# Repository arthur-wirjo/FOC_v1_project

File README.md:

# DIY FOC Motor Controller V1: Custom Hardware & Firmware from Scratch 

A custom-designed, 60V 50A Field Oriented Control (FOC) BLDC motor controller built from scratch. Designed for high-performance robotics, featuring a 4-layer power PCB, isolated USB telemetry, and CAN bus communication.

## Overview

I started this project to deeply understand the hardware architecture of modern, high-power motor drivers like the VESC and ODrive. Instead of just buying an off-the-shelf driver, I wanted to design one from the ground up to learn the intricacies of power electronics, mixed-signal PCB layout, gate driving, and hardware debugging.

The system is split into a 4-layer main power board (handling the MCU and 60V power stage) and a separate 2-layer magnetic encoder board mounted directly to the motor. This approach kept the overall footprint compact and reduced manufacturing costs.

As the project progressed, it evolved beyond "build a VESC clone" into writing a full custom bare-metal FOC firmware stack from scratch. As of October 3, 2026, the board successfully runs closed-loop Field-Oriented Control, achieving smooth velocity control. Having fulfilled its purpose as a deep-dive educational tool into power electronics and motor control theory, **this project is now officially concluded**. The repository remains as a documented post-mortem and reference for DIY FOC development.

## Key Features

* **Working Closed-Loop FOC:** Fully custom bare-metal firmware achieves smooth closed-loop current control and velocity control.
* **60V Power Stage:** 60V-rated MOSFETs capable of handling 10S Li-Po battery voltages and regenerative braking spikes.
* **Precision Current Sensing:** 1mΩ shunt resistors utilizing strict Kelvin connections and RC-filtered differential amplifiers.
* **Isolated Telemetry:** ADuM3160-based USB isolation to protect the host computer from catastrophic 60V transients during live tuning.
* **Robust Communication:** TJA1051T/3 CAN bus transceiver with 120Ω termination for robot networking.
* **Modular Encoder:** Separate 2-layer AS5048A magnetic encoder PCB using JST-GH SMD connectors.

## Hardware

### Computing & Control
* **Microcontroller:** STM32F405RGT6 (Chosen for its floating-point unit, advanced motor control timers, and native VESC compatibility)
* **Gate Driver:** TI DRV8301 (Features a built-in 5V buck converter and dual current shunt amplifiers. Chosen over the DRV8323 for VESC compatibility)

### Power Stage
* **MOSFETs:** Infineon IRFS7530 in D2PAK-7 (Rated for 60V, providing ample headroom for a 10S ~40V battery and regenerative braking)
* **Current Sense:** Yageo PU2512FK-070R001L (1mΩ, 2W metal alloy shunts)
* **Protection:** Littelfuse SMCJ43A TVS Diode (Clamps dangerous voltage spikes generated by motor back-EMF during hard braking)
* **Connectors:** Amass XT90-S (Anti-spark) for battery input

### Sensing & Telemetry
* **Encoder:** AMS AS5048A (14-bit absolute magnetic encoder reading a 6x2.5mm diametrically magnetized NdFeB magnet)
* **Temperature:** Murata 10kΩ 0603 NTC Thermistor (Placed directly adjacent to the MOSFETs to monitor power stage thermals)
* **Voltage Sensing:** 39kΩ / 2.2kΩ voltage divider to safely scale the 60V bus down to the STM32's 3.3V ADC range

## PCB Design & Layout

The board utilizes a 4-layer stackup to safely separate high-current paths from delicate digital signals:
* **Layer 1 (Top):** Components, massive copper polygons for Motor Phases and 42V supply.
* **Layer 2 (Inner 1):** Solid GND plane (Acts as an EMI shield for the signal layer).
* **Layer 3 (Inner 2):** Signal routing (SPI, CAN, Gate Drive traces).
* **Layer 4 (Bottom):** Additional GND and 42V copper pours, heavily via-stitched to the top layer to maximize current carrying capacity and thermal dissipation.

## Challenges and Lessons Learned

Building a high-power motor controller from scratch provided an intense, hands-on education in hardware and firmware debugging.

### Solder Wicking and Clearance Tolerances (V1.0)
After freshly soldering the V1.0 PCB, I felt an unusually strong resistance when I tried to rotate the motor by hand. I learned this is caused by back-EMF when phase wires are shorted together. Multimeter testing confirmed that V++, GND, and all three motor phases were dead-shorted.

Upon inspection, I realized the clearance between my GND copper pour and the soldering pads for V++ and the phase wires was very small (0.15mm). When hand-soldering the massive motor wires, the liquid solder easily wicked across that tiny gap into the GND pour.

For V1.1, I redesigned the board with strict Net Classes, increasing the clearance around high-power wire pads to 0.6mm to create a physical "moat", while keeping the MCU digital clearance at 0.15mm for dense routing.

### The "Bad Internet Symbol" Trap (V1.1)
After successfully assembling V1.1 with new stencils and corrected clearances, the board still exhibited a short between V++, GND, and the phase wires.

I started isolating the issue by desoldering components one by one. I checked a bare V1.0 board and found no shorts, meaning the layout itself wasn't fundamentally shorted. I desoldered the MCU and gate driver — the short was still there. Finally, I desoldered the high-side MOSFETs one by one. Removing the last high-side MOSFET finally severed the short between V++ and the motor phases.

I probed the desoldered MOSFET and found a short between Pin 7 and the Source pins (Pins 2-6). Initially, I thought the MOSFET had overheated and failed closed during hot-plate reflow. However, I looked into the Infineon datasheet and saw a catastrophic error in the third-party CAD symbol I had downloaded.

The symbol incorrectly labeled Pin 7 as "Drain". In reality, the D2PAK-7 package uses the large back EPAD as the Drain, and Pins 2 through 7 are *all* Source pins. Because I followed the flawed schematic, my PCB layout drew a massive copper pour that physically connected the Drain (EPAD) to the Source (Pin 7). The PCB itself was shorting the circuit by design, while the MOSFETs were actually unharmed.

**Lesson learned:** Never trust third-party CAD footprints without verifying against the manufacturer's datasheet.

### The USB D+/D- Swap (V1.2)
With the phase-short issue resolved, V1.2 soldered up cleanly with no shorts between V++, GND, or the phase wires. After hours of VESC firmware macro configuration, I successfully flashed VESC firmware onto the board. However, the board never enumerated over USB — nothing populated on the host PC.

I re-checked the firmware configuration and it looked correct, so I moved to the hardware. It turned out to be a wiring mistake on my end, though the confusing pin naming in the schematic symbol didn't help: instead of connecting DP1↔DP2 and DN1↔DN2 (the isolator-side and MCU-side USB differential pairs), I had wired DP1↔DN1 and DP2↔DN2 — crossing the differential pairs instead of linking them straight through. I corrected this for V1.3.

### The Mysterious Non-Enumerating USB (V1.3)
V1.3 fixed the DP/DN wiring mistake. USB still did not enumerate.

At this point I was confident the hardware was correct, so I wrote a minimal bare-metal STM32 firmware (via STM32CubeMX, STM32CubeIDE, and STM32CubeProgrammer) with nothing but a USB CDC "hello world" to test enumeration independently of VESC firmware. It worked immediately — the host PC detected the board and the virtual COM port came up cleanly. This confirmed the hardware (including the USB isolation and the DP/DN fix) was fine, and the problem was somewhere inside VESC firmware itself.

After a weekend of digging, my working theory is that VESC firmware assumes VBUS sensing on a specific pin by default, which on my board doesn't correspond to an actual VBUS-sensing net — that pin (PA9 / TIM1_CH2) is repurposed as a motor PWM output on my hardware. If VESC firmware is waiting on a VBUS-sense signal that physically doesn't exist on my board, USB enumeration would never complete, since the firmware assumes the connection is dead.

Rather than dig further into VESC's fairly large and unfamiliar codebase to patch around this, I decided to use this as an opportunity to learn embedded systems more deeply from first principles by writing my own bare-metal FOC firmware from scratch.

### The Deceiving Cogging Torque (Open-Loop Commutation)
After first achieving open-loop commutation, I later struggled to reproduce it and assumed something had regressed in the firmware. After investigation, I realized the real cause: during my initial successful test, the motor had warmed up from repeated open-loop parameter tuning, which reduced its cogging torque (magnetic detent force) enough for the open-loop drive to overcome it smoothly. On a cold motor, the same open-loop parameters weren't enough to break through cogging torque cleanly. This was a good reminder that motor behavior is temperature-dependent, and that "it worked once" isn't the same as "it's tuned correctly."

### Missing Bulk Decoupling Capacitor (Current Sensing Noise)
While debugging noisy phase current readings, a senior pointed out that the DRV8301's built-in 5V buck converter was missing a bulk decoupling capacitor on my board. Without it, switching-induced ripple on the 5V rail was likely feeding through to the gate driver's built-in current sense amplifiers, degrading signal quality. I added the missing capacitor directly onto the existing V1.3 board (Frankenstein-style, dead-bug soldered), which noticeably cleaned up the current readings enough for stable closed-loop control. This will be properly integrated into the layout for the next PCB revision.

### Current Sensing Offsets and Phase Anomalies (The Final Hurdle)
While closed-loop velocity control was achieved, the final hurdle involved anomalies in the low-side current sensing. Through telemetry analysis under load, I observed three distinct issues:
1. **DC Offsets:** Despite software calibration, i_a exhibited a heavy positive offset (min -0.05A, max 0.35A), i_b (calculated) had a heavy negative offset, and i_c was relatively balanced. This points to inherent analog front-end biases or layout-induced ground offsets.
2. **Noise:** Low-side sensing is notoriously susceptible to switching noise. Even with ADC sampling synchronized to the timer's update event (the "quiet window"), the raw data remained spiky, pushing the limits of the software's low-pass filters.
3. **The 180-Degree Phase Shift Anomaly:** Telemetry revealed that i_a and i_c appeared to be roughly 180 degrees out of phase, rather than the expected 120 degrees. Initially, one might suspect a flipped differential pair on the PCB, but mathematically, inverting a 120-degree signal results in a 300-degree (-60 degree) phase shift, not 180 degrees. This anomaly is much more likely an artifact of severe layout-induced noise, ground bounce, or the inherent limitations of low-side current sensing on a noisy DIY board skewing the reconstructed waveforms.

**Lesson learned:** Mixed-signal PCB layout for high-current switching requires extreme care. For V2, I would transition to in-line current sensing with dedicated isolated amplifiers, ensure perfectly matched differential pair routing for the shunts, and implement a more robust analog filtering stage.

## Custom Firmware Development

Since abandoning VESC firmware, I built a custom bare-metal firmware stack using STM32CubeMX, STM32CubeIDE, and FreeRTOS (for telemetry and state management), with the actual FOC control loop implemented as a hardware-timer/ADC-interrupt-driven routine.

### MCU Pinout

**PWM (TIM1, Center-Aligned, Complementary Outputs)**
| Pin | Function |
|---|---|
| PA8 | TIM1_CH1 |
| PA9 | TIM1_CH2 |
| PA10 | TIM1_CH3 |
| PB13 | TIM1_CH1N |
| PB14 | TIM1_CH2N |
| PB15 | TIM1_CH3N |

**ADC (Current & Voltage Sensing)**
| Pin | Function |
|---|---|
| PA0 | ADC1_IN0 — Phase A Current |
| PA1 | ADC2_IN1 — Phase C Current |
| PA2 | ADC3_IN2 — VBUS Voltage Sensing |
| PA3 | ADC3_IN3 — MOSFET Temperature |

**DRV8301 Gate Driver (SPI1)**
| Pin | Function |
|---|---|
| PC1 | EN_GATE |
| PC2 | DC_CAL |
| PC0 | nFAULT (EXTI0) |
| PB3 | SPI1_SCK |
| PB4 | SPI1_MISO |
| PB5 | SPI1_MOSI |
| PD2 | CS |

**Encoder (SPI3)**
| Pin | Function |
|---|---|
| PC10 | SPI3_SCK |
| PC11 | SPI3_MISO |
| PC12 | SPI3_MOSI |
| PA15 | CS |

**CAN**
| Pin | Function |
|---|---|
| PB8 | CAN1_RX |
| PB9 | CAN1_TX |

**USB**
| Pin | Function |
|---|---|
| PA11 | D- |
| PA12 | D+ |

> **Critical note:** VBUS sensing on PA9 is intentionally *not* used — PA9 is a motor PWM pin on this board (see the V1.3 debugging story above). USB is forced to enumerate without relying on VBUS sensing.

### STM32CubeMX Configuration Notes
* Deadtime configured on the PWM timer to prevent shoot-through.
* Center-aligned PWM mode for reduced current ripple.
* ADC sampling is hardware-synchronized to PWM switching using TIM1's "Update Event" as the ADC "Trigger Event Selection," so current is always sampled at a consistent point in the switching cycle.
* Third phase current is reconstructed using Kirchhoff's Current Law rather than measured directly (only two shunts are sensed).
* ADC current sensing uses **injected conversion mode** so it can be hardware-triggered directly by the timer.
* ADC interrupt enabled in NVIC settings for the current-sensing ADC.
* Encoder SPI configured with DMA in full-duplex master mode.
* USB configured using the USB CDC class for direct serial communication with the host PC.

### Firmware Development Progress
1. ✅ Pinout and hardware configuration in CubeMX
2. ✅ USB CDC enumeration working
3. ✅ DRV8301 register read helper function + gate driver wake-up sequence
4. ✅ SPI encoder DMA callback
5. ✅ Open-loop SPWM commutation and tuning
6. ✅ DRV8301 register write helper function for current amplifier gain configuration
7. ✅ ADC hardware interrupt callback for current sensing (`HAL_ADC_ConvCpltCallback`)
8. ✅ FOC algorithm implemented inside `HAL_ADC_ConvCpltCallback`
9. ✅ Closed-loop current control achieved
10. ✅ Closed-loop velocity control achieved — smooth motor spin under true FOC

### Current Firmware State (Final)
* Closed-loop Field-Oriented Control is working on hardware: the motor spins smoothly under closed-loop velocity control.
* Open-loop SPWM commutation, ADC-synchronized current sensing, and gate driver configuration are validated.
* **Future Improvements (Left as an exercise for V2):** Transitioning to in-line current sensing to resolve the noise and phase shift anomalies, implementing automatic motor R and L measurement, and adding trajectory generation (slew-rate limiting) for smoother bidirectional startups.

## Current Status
* **V1.0 & V1.1:** Deprecated — used for footprint verification and short-circuit debugging (solder wicking clearance issue, mislabeled MOSFET footprint).
* **V1.2:** Deprecated — resolved the phase-short issues from V1.0/V1.1, but had a USB differential pair wiring mistake (DP/DN crossed) that prevented USB enumeration.
* **V1.3 (Final):** USB wiring fixed and verified via custom bare-metal USB CDC test firmware. Pivoted to a fully custom bare-metal FOC firmware stack. Closed-loop FOC achieved and validated on hardware. Smooth closed-loop velocity control is working. The project is now officially closed, serving as a successful proof-of-concept and an invaluable learning experience in embedded systems and power electronics.

## Project Timeline

| Date | Milestone |
|---|---|
| Jun 5 | Project start |
| Jun 19 | Theory research complete |
| Jul 2 | Schematic & component sourcing complete |
| Jul 13 | V1.0 PCB layout complete |
| Jul 23 | V1.0 assembled |
| Jul 27 | V1.0 testing — discovered phase/GND short from insufficient copper clearance (0.15mm) |
| Jul 30 | V1.1 redesigned with wider clearances |
| Aug 22 | V1.1 assembled — short persisted |
| — | Root cause found: mislabeled MOSFET footprint (Drain/Source swap) |
| Aug 28 | V1.2 arrives (footprint fixed) |
| — | Discovered incorrect USB D+/D- wiring |
| Sep 9 | V1.3 arrives (USB wiring corrected) |
| Sep 13 | Began VESC firmware integration — blocked by USB enumeration failure |
| Sep 17 | Diagnosed VBUS-sensing conflict; pivoted to custom bare-metal firmware |
| Sep 19 | Open-loop commutation achieved (later traced intermittent failures to motor-temperature-dependent cogging torque) |
| Sep 22 | ADC current sensing achieved (noisy — later traced to missing decoupling capacitor) |
| Sep 24 | Fixed missing decoupling capacitor; current sensing quality improved |
| Sep 25 | Closed-loop current control achieved |
| Sep 28 | Closed-loop velocity control achieved — true FOC working |
| **Oct 3** | **Telemetry analysis completed. Project officially concluded and documented as a post-mortem.** |

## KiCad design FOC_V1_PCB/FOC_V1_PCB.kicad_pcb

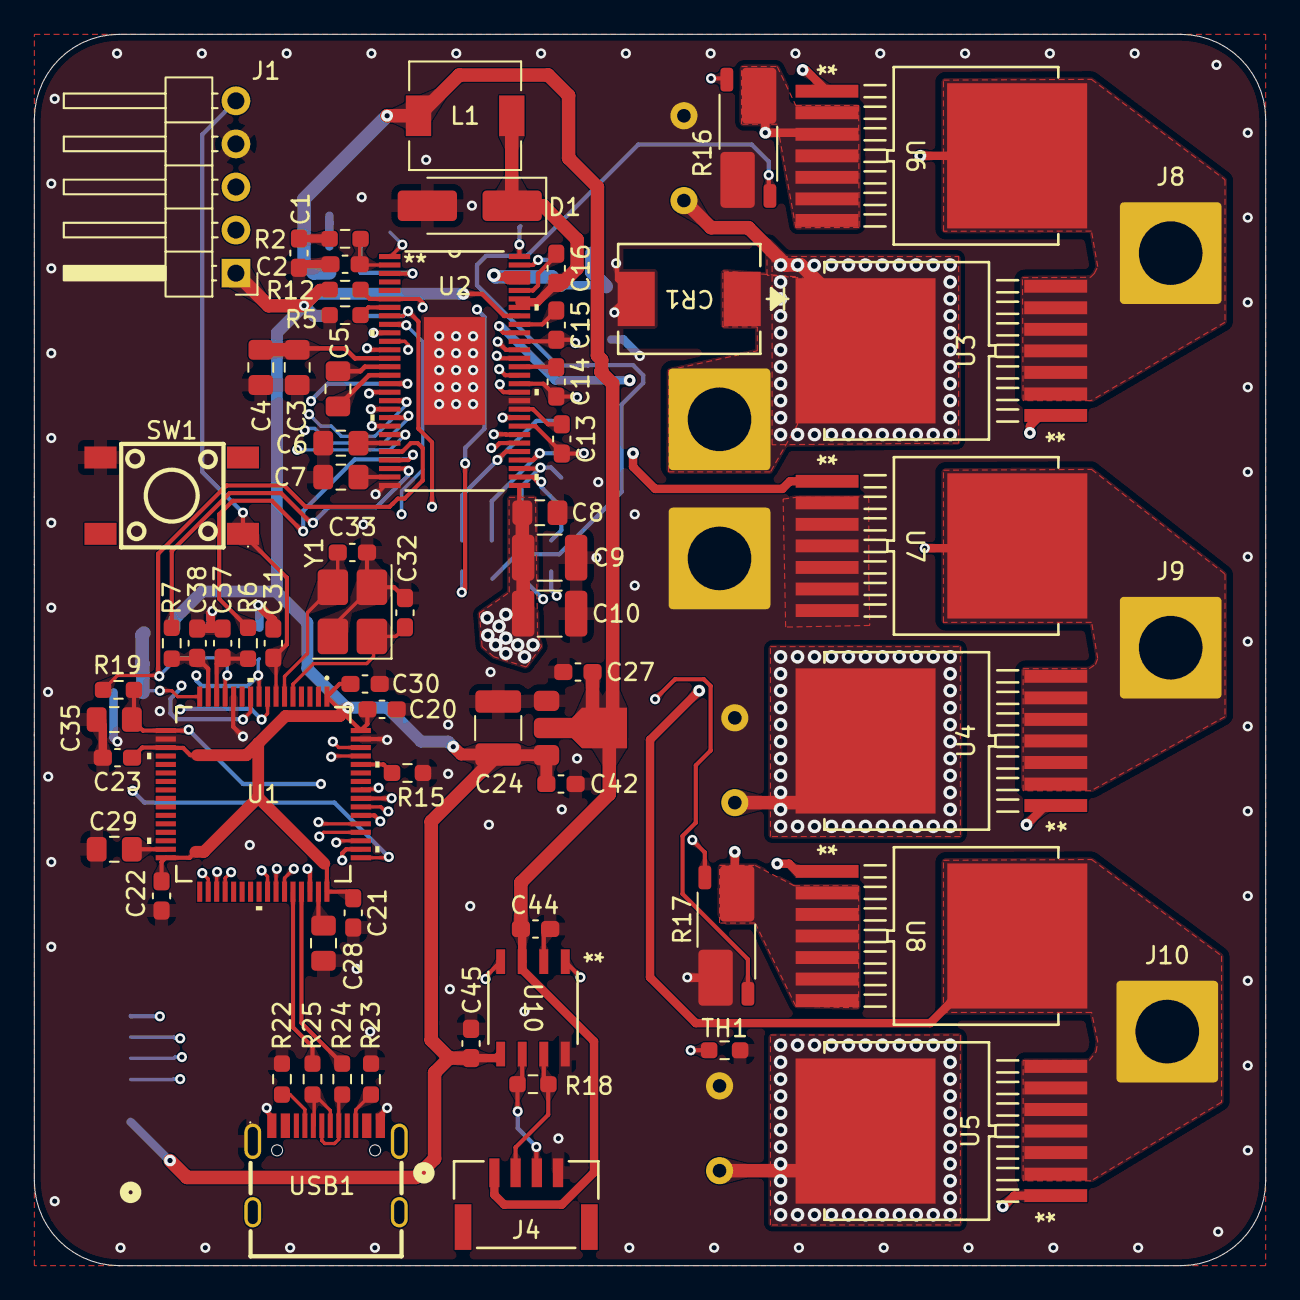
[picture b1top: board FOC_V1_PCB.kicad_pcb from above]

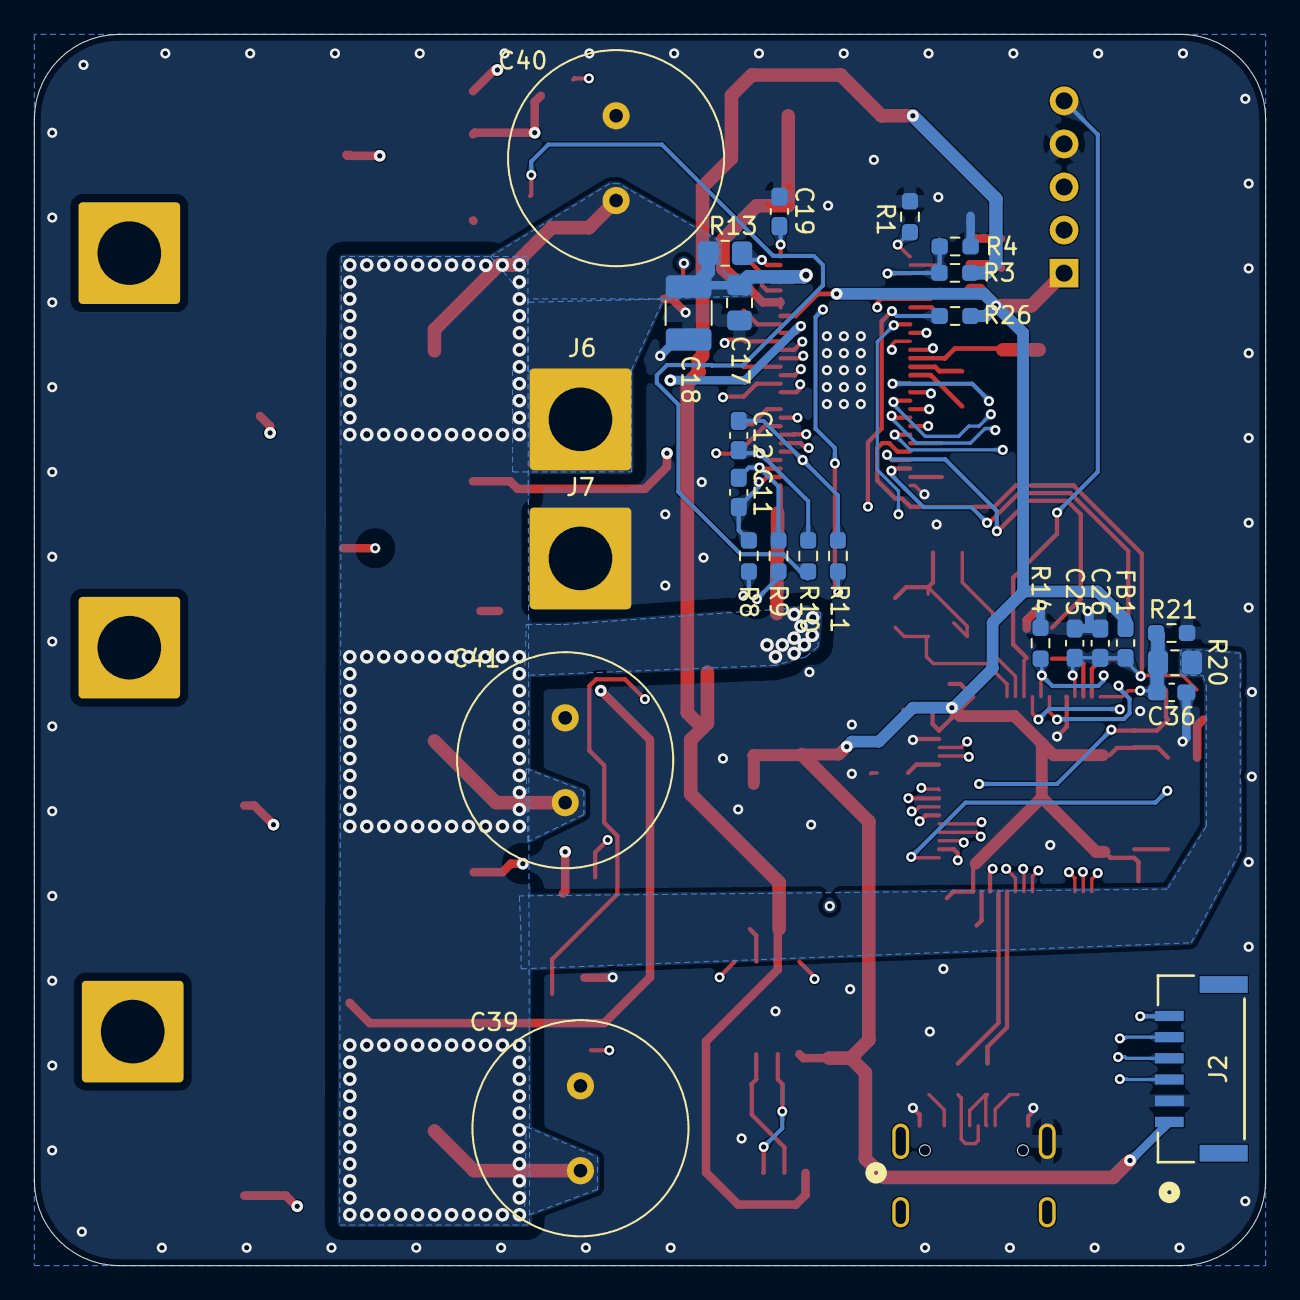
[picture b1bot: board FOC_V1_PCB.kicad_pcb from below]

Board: 4 copper layers, 72.6 x 72.6 mm, 95 parts (27 on the bottom side), 82 nets.

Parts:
C1: 6.8nF; C_0603_1608Metric_Pad1.08x0.95mm_HandSolder
C2: 120pF; C_0603_1608Metric_Pad1.08x0.95mm_HandSolder
C3, C4: 2.2μF; C_0805_2012Metric_Pad1.18x1.45mm_HandSolder
C5: 22nF; C_0805_2012Metric_Pad1.18x1.45mm_HandSolder
C6, C7, C28, C29, C35: 2.2µF; C_0805_2012Metric_Pad1.18x1.45mm_HandSolder
C8, C17: 100nF; C_0805_2012Metric_Pad1.18x1.45mm_HandSolder
C9, C10, C18: 4.7µF; C_1210_3225Metric_Pad1.33x2.70mm_HandSolder
C11, C12, C37, C38: 2.2nF; C_0603_1608Metric_Pad1.08x0.95mm_HandSolder
C13, C14, C15: 220nF; C_0603_1608Metric_Pad1.08x0.95mm_HandSolder
C16, C20, C21, C22, C23, C30, C31, C36, C44, C45: 100nF; C_0603_1608Metric_Pad1.08x0.95mm_HandSolder
C19: 15nF; C_0603_1608Metric_Pad1.08x0.95mm_HandSolder
C24: 10µF; C_1210_3225Metric_Pad1.33x2.70mm_HandSolder
C25, C27, C42: 1µF; C_0603_1608Metric_Pad1.08x0.95mm_HandSolder
C26: 10nF; C_0603_1608Metric_Pad1.08x0.95mm_HandSolder
C32, C33: 15pF; C_0603_1608Metric_Pad1.08x0.95mm_HandSolder
C39, C40, C41: 470µF; C_Radial_D12.5mm_H20.0mm_P5.00mm
CR1: SMCJ43A; TVS_Diode_SMCJSeries_LTF
D1: D_Schottky; D_SMA_Handsoldering
FB1: FerriteBead; L_0603_1608Metric_Pad1.05x0.95mm_HandSolder
J1: ST-Link_01x05; PinHeader_1x05_P2.54mm_Horizontal
J2: Enc_MCU_01x06; JST-GH_6pin_CONN_SM06B-GHS-TB_JST
J4: CAN_01x04; JST-GH_4pin_CONN_SM04B-GHS-TB_JST
J6: +V; SolderWire-4sqmm_1x01_D3mm_OD6mm
J7: GND; SolderWire-4sqmm_1x01_D3mm_OD6mm
J8: A; SolderWire-4sqmm_1x01_D3mm_OD6mm
J9: B; SolderWire-4sqmm_1x01_D3mm_OD6mm
J10: C; SolderWire-4sqmm_1x01_D3mm_OD6mm
L1: 22µH; L_6.3x6.3_H3
R1: 205kΩ; R_0603_1608Metric_Pad0.98x0.95mm_HandSolder
R2: 16.2kΩ; R_0603_1608Metric_Pad0.98x0.95mm_HandSolder
R3: 52.3kΩ; R_0603_1608Metric_Pad0.98x0.95mm_HandSolder
R4, R5, R12, R14, R15, R19, R26: 10kΩ; R_0603_1608Metric_Pad0.98x0.95mm_HandSolder
R6, R7: 56Ω; R_0603_1608Metric_Pad0.98x0.95mm_HandSolder
R8, R9, R10, R11: 100Ω; R_0603_1608Metric_Pad0.98x0.95mm_HandSolder
R13: 100kΩ; R_0805_2012Metric_Pad1.20x1.40mm_HandSolder
R16, R17: R_Shunt; R_Shunt_Vishay_WSK2512_6332Metric_T2.66mm
R18: 120Ω; R_0603_1608Metric_Pad0.98x0.95mm_HandSolder
R20: 39kΩ; R_0805_2012Metric_Pad1.20x1.40mm_HandSolder
R21: 2.2kΩ; R_0603_1608Metric_Pad0.98x0.95mm_HandSolder
R22, R23: 5.1kΩ; R_0603_1608Metric_Pad0.98x0.95mm_HandSolder
R24, R25: 22Ω; R_0603_1608Metric_Pad0.98x0.95mm_HandSolder
SW1: TS-1002S-05026C; Button_KEY-SMD_4P-L6.0-W6.0-P4.50-LS9.0
TH1: 10kΩ Thermistor_NTC; R_0603_1608Metric_Pad0.98x0.95mm_HandSolder
U1: STM32F405RGT6; STM32F405_LQFP64-10x10mm
U2: DRV8301DCAR; DRV8301_DCA56_6P35X3P61
U3, U4, U5, U6, U7, U8: IRFS7530TRL7PP; IRFS7530_PG-TO263-7_INF
U10: TJA1051T/3/1J; TJA1051_SO8_SOT96-1_NXP
U11: ME6211; ME6211A33PG-N_SOT89-3
USB1: HYCW498-USBC16-735B; USB-C-SMD_HYCW498-USBC16-735B
Y1: Crystal_GND24; Crystal_SMD_3225-4Pin_3.2x2.5mm_HandSoldering

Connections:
BUCK_+5V: C27.2, C44.1, J4.1, L1.2, R3.2, U10.3 (VCC), U11.2 (VIN)
CAN_H: J4.2, R18.1, U10.7 (CANH)
CAN_L: J4.3, R18.2, U10.6 (CANL)
DRV_DC_CAL: U1.10 (PC2), U2.12 (DC_CAL)
DRV_EN_GATE: R14.1, U1.9 (PC1), U2.16 (EN_GATE)
DRV_GH_A: U2.47 (GH_A), U3.1 (G)
DRV_GH_B: U2.42 (GH_B), U4.1 (G)
DRV_GH_C: U2.37 (GH_C), U5.1 (G)
DRV_GL_A: U2.45 (GL_A), U6.1 (G)
DRV_GL_B: U2.40 (GL_B), U7.1 (G)
DRV_GL_C: U2.35 (GL_C), U8.1 (G)
DRV_HA: U1.41 (PA8), U2.17 (INH_A)
DRV_HB: U1.42 (PA9), U2.19 (INH_B)
DRV_HC: U1.43 (PA10), U2.21 (INH_C)
DRV_LA: U1.34 (PB13), U2.18 (INL_A)
DRV_LB: U1.35 (PB14), U2.20 (INL_B)
DRV_LC: U1.36 (PB15), U2.22 (INL_C)
DRV_SH_A: C15.2, J8.1 (Pin_1_1), U2.46 (SH_A), U3.2 (S), U3.3 (S), U3.4 (S), U3.5 (S), U3.6 (S), U3.7 (S), U6.8 (EPAD)
DRV_SH_B: C14.2, J9.1 (Pin_1_1), U2.41 (SH_B), U4.2 (S), U4.3 (S), U4.4 (S), U4.5 (S), U4.6 (S), U4.7 (S), U7.8 (EPAD)
DRV_SH_C: C13.2, J10.1 (Pin_1_1), U2.36 (SH_C), U5.2 (S), U5.3 (S), U5.4 (S), U5.5 (S), U5.6 (S), U5.7 (S), U8.8 (EPAD)
DRV_SL_A: R16.1, U2.44 (SL_A), U6.2 (S), U6.3 (S), U6.4 (S), U6.5 (S), U6.6 (S), U6.7 (S)
DRV_SL_C: R17.1, U2.34 (SL_C), U8.2 (S), U8.3 (S), U8.4 (S), U8.5 (S), U8.6 (S), U8.7 (S)
DRV_SN1: R11.2, R16.2
DRV_SN2: R9.2, R17.2
DRV_SO1: R6.1, U2.25 (SO1)
DRV_SO2: R7.2, U2.26 (SO2)
DRV_SP1: R10.2, R16.3
DRV_SP2: R8.2, R17.3
DRV_SPI_SCLK: U1.55 (PB3), U2.11 (SCLK)
DRV_SPI_SCS: R26.1, U1.54 (PD2), U2.8 (*SCS)
DRV_SPI_SDI: U1.57 (PB5), U2.9 (SDI)
DRV_SPI_SDO: U1.56 (PB4), U2.10 (SDO)
DRV_nFAULT: R12.1, U1.8 (PC0), U2.6 (*FAULT)
ENC_SPI_SCLK: J2.3, U1.51 (PC10)
ENC_SPI_SCS: J2.6, U1.50 (PA15)
ENC_SPI_SDI: J2.5, U1.53 (PC12)
ENC_SPI_SDO: J2.4, U1.52 (PC11)
GND: C1.2, C2.2, C3.2, C4.2, C6.1, C7.1, C8.2, C9.2, C10.2, C17.2, C18.2, C19.2, C20.2, C21.2, C22.2, C23.2, C24.2, C25.1, C26.1, C27.1, C28.1, C29.1, C30.2, C31.2, C32.2, C33.2, C35.2, C36.2, C37.2, C38.1, C39.2, C40.2, C41.2, C42.2, C44.2, C45.2, CR1.2, D1.2 (A), J1.4, J2.2, J4.4, J7.1 (Pin_1_1), R1.1, R4.2, R5.1, R14.2, R15.2, R16.4, R17.4, R21.2, R22.2, R23.2, SW1.4, TH1.2, U1.12 (VSSA), U1.18 (VSS), U1.63 (VSS), U2.28 (AGND), U2.39 (SL_B), U2.57 (EPAD), U7.2 (S), U7.3 (S), U7.4 (S), U7.5 (S), U7.6 (S), U7.7 (S), U10.2 (GND), U10.8 (S), U11.1 (VSS), USB1.1 (SHELL), USB1.A1B12 (GND), USB1.B1A12 (GND), Y1.2 (G), Y1.4 (G)
LDO_+3.3V: C20.1, C21.1, C22.1, C23.1, C24.1, C30.1, C42.1, C45.1, FB1.2, J1.1, J2.1, R12.2, R26.2, U1.1 (VBAT), U1.19 (VDD), U1.32 (VDD), U1.48 (VDD), U1.64 (VDD), U2.49 (VDD_SPI), U10.5 (VIO), U11.3 (VOUT)
MCU_BUS_VSENSE: C36.1, R20.2, R21.1, U1.16 (PA2)
MCU_CAN_RX: U1.61 (PB8), U10.4 (RXD)
MCU_CAN_TX: U1.62 (PB9), U10.1 (TXD)
MCU_NRST: C31.1, J1.5, SW1.1, U1.7 (NRST)
MCU_NTC: C35.1, R19.2, TH1.1, U1.17 (PA3)
MCU_SWCLK: J1.3, U1.49 (PA14)
MCU_SWDIO: J1.2, U1.46 (PA13)
MCU_USB_DM: R25.2, U1.44 (PA11)
MCU_USB_DP: R24.2, U1.45 (PA12)
MCU_VDDA: C25.2, C26.2, FB1.1, R19.1, U1.13 (VDDA), U2.24 (REF)
unnamed: C1.1, R2.2
unnamed: C16.2, D1.1 (K), L1.1, U2.50 (PH), U2.51 (PH)
unnamed: R15.1, U1.60 (BOOT0)
unnamed: C37.1, R6.2, U1.14 (PA0/WKUP)
unnamed: C38.2, R7.1, U1.15 (PA1)
unnamed: C32.1, U1.5 (PH0/OSC_IN), Y1.1
unnamed: C33.1, U1.6 (PH1/OSC_OUT), Y1.3
unnamed: C29.2, U1.31 (VCAP_1)
unnamed: C28.2, U1.47 (VCAP_2)
unnamed: C7.2, U2.27 (AVDD)
unnamed: C15.1, U2.48 (BST_A)
unnamed: C14.1, U2.43 (BST_B)
unnamed: C16.1, U2.52 (BST_BK)
unnamed: C13.1, U2.38 (BST_C)
unnamed: C2.1, R2.1, U2.2 (COMP)
unnamed: C5.1, U2.14 (CP1)
unnamed: C5.2, U2.15 (CP2)
unnamed: R5.2, U2.7 (DTC)
unnamed: C6.2, U2.23 (DVDD)
unnamed: R13.1, U2.55 (EN_BUCK)
unnamed: C3.1, C4.1, U2.13 (GVDD)
unnamed: R1.2, U2.1 (RT_CLK)
unnamed: C12.1, R11.1, U2.33 (SN1)
unnamed: C11.1, R9.1, U2.31 (SN2)
unnamed: C12.2, R10.1, U2.32 (SP1)
unnamed: C11.2, R8.1, U2.30 (SP2)
unnamed: C19.1, U2.56 (SS_TR)
unnamed: R3.1, R4.1, U2.3 (VSENSE)
unnamed: R22.1, USB1.A5 (CC1)
unnamed: R23.1, USB1.B5 (CC2)
unnamed: R25.1, USB1.A7 (DN1), USB1.B7 (DN2)
unnamed: R24.1, USB1.A6 (DP1), USB1.B6 (DP2)
V_Supply_+42V: C8.1, C9.1, C10.1, C17.1, C18.1, C39.1, C40.1, C41.1, CR1.1, J6.1 (Pin_1_1), R13.2, R20.1, U2.29 (PVDD1), U2.53 (PVDD2), U2.54 (PVDD2), U3.8 (EPAD), U4.8 (EPAD), U5.8 (EPAD)

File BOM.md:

### Main FOC Board BOM

| Category | Description / Value | Manufacturer & Part Number | Designator | Qty |
| :--- | :--- | :--- | :--- | :--- |
| **Capacitors** | 15pF, 0603, C0G, 25V | muRata GCM1885C2A150FA16D | C32, C33 | 2 |
| | 120pF, 0603, C0G, 25V | muRata GCM1885C2A121FA16D | C2 | 1 |
| | 2.2nF, 0603, X7R, 25V | Samsung Electro-Mechanics CL10B222KB8NNN | C11, C12, C37, C38 | 4 |
| | 6.8nF, 0603, X7R, 25V | Samsung Electro-Mechanics CL10B682JB8NNNC | C1 | 1 |
| | 10nF, 0603, X7R, 25V | Samsung Electro-Mechanics CL10B103KC8NNNC | C26 | 1 |
| | 15nF, 0603, X7R, 25V | Samsung Electro-Mechanics CL10B153KB8NNNC | C19 | 1 |
| | 22nF, 0805, X7R, 100V | Samsung Electro-Mechanics CL21B223KCFWPJE | C5 | 1 |
| | 100nF, 0603, X7R, 25V | Samsung Electro-Mechanics CL10B104KA8NNNC | C16, C20–C23, C30, C31, C36, C44, C45 | 10 |
| | 100nF, 0805, X7R, 100V | Samsung Electro-Mechanics CL21B104KCFWPNE | C8, C17 | 2 |
| | 220nF, 0603, X7R, 25V | Samsung Electro-Mechanics CL10B224KA8NFNC | C13, C14, C15 | 3 |
| | 1uF, 0603, X7R, 25V | YAGEO CS0603KRX7R8BB105 | C25, C27, C42 | 3 |
| | 2.2uF, 0805, X7R, 25V | Samsung Electro-Mechanics CL21B225KAFNNNE | C3, C4, C6, C7, C28, C29, C35 | 7 |
| | 4.7uF, 1210, X7R, 100V | Samsung Electro-Mechanics CL32B475KCJZ4NE | C9, C10, C18 | 3 |
| | 10uF, 1210, X7R, 25V | Samsung Electro-Mechanics CL32B106KAJNNNE | C24 | 1 |
| | 470uF, Aluminium Electrolytic, 80V | Ymin LKML2001K471MF | C39, C40, C41 | 3 |
| **Resistors** | 22Ω, 0603, 1% | UNI-ROYAL HP03W5F220JT5E | R24, R25 | 2 |
| | 56Ω, 0603, 1% | UNI-ROYAL HP03W5F560JT5E | R6, R7 | 2 |
| | 100Ω, 0603, 1% | UNI-ROYAL HP03W5F1000T5E | R8, R9, R10, R11 | 4 |
| | 120Ω, 0603, 1% | UNI-ROYAL PS03W4F1200T5E | R18 | 1 |
| | 2.2kΩ, 0603, 1% | UNI-ROYAL HP03W5F2201T5E | R21 | 1 |
| | 5.1kΩ, 0603, 1% | YAGEO AC0603FR-075K1L | R22, R23 | 2 |
| | 10kΩ, 0603, 1% | FH ABD03K1002FT | R4, R5, R12, R14, R15, R19, R26 | 7 |
| | 16.2kΩ, 0603, 1% | FH RS-03K1622FT | R2 | 1 |
| | 39kΩ, 0805, 1% | FH RS-05K3902FT | R20 | 1 |
| | 52.3kΩ, 0603, 1% | UNI-ROYAL 0603WAF5232T5E | R3 | 1 |
| | 100kΩ, 0805, 1% | FH RS-05K1003FT | R13 | 1 |
| | 205kΩ, 0603, 1% | UNI-ROYAL 0603WAF2053T5E | R1 | 1 |
| | Shunt Resistor | JIERR JER2512F2R001L | - | 2 |
| | NTC Thermistor | muRata NCP18XH103F03RB | - | 1 |
| **ICs & Semis** | Microcontroller | ST STM32F405RGT6 | - | 1 |
| | Gate Driver | TI DRV8301DCAR | - | 1 |
| | Power MOSFET | Infineon IRFS7530TRL7PP0 | - | 6 |
| | LDO | MICRONE ME6211A33PG-N | - | 1 |
| | CAN Transceiver | ZHHXDZ TJA1051T/3/1J-HX | - | 1 |
| | Schottky Diode | MDD SS310 | - | 1 |
| | TVS Diode | Littelfuse SMCJ43A | - | 1 |
| **Passives / Misc** | Inductor | ZE ZNR6045ST220M | - | 1 |
| | Ferrite Bead | muRata BLM18SP601SH1D | - | 1 |
| | Crystal | YXC X32258MOB4SI | - | 1 |
| | Button | XUNPU TS-1002S-05026C | - | 1 |
| **Connectors** | USB-C Receptacle (USB 2.0, 16-pin) | HOAUC HYCW498-USBC16-735B | - | 1 |
| | 2.54mm pitch 5-pin male header | - | - | 1 |
| | JST-GH 6-pin male header (SMD) | - | - | 1 |
| | JST-GH 4-pin male header (SMD) | - | - | 1 |

### Encoder Board BOM

| Category | Description / Value | Manufacturer & Part Number | Designator | Qty |
| :--- | :--- | :--- | :--- | :--- |
| **ICs** | Magnetic Encoder | ams AS5048A-HTSP-500 | - | 1 |
| **Capacitors** | 100nF, 0603, X7R, 25V | Samsung Electro-Mechanics CL10B104KA8NNNC | C34 | 1 |
| **Resistors** | 10kΩ, 0603, 1% | FH ABD03K1002FT | R27 | 1 |
| **Connectors** | JST-GH 6-pin male header (SMD) | - | - | 1 |

### Off-Board Components (Cables & Tools)

| Category | Description / Value | Details / Specifications | Qty |
| :--- | :--- | :--- | :--- |
| **Cables** | Encoder Wires | JST-GH 6-pin | 1 |
| | CAN Wires | JST-GH 4-pin | 1 |
| | Power Cables | 4mm banana plug to XT60 connector, silicone wire | 1 |
| **Tools & Dongles** | USB Isolator Dongle | ADuM3160 Digital Signal / Power USB Isolator | 1 |
| | Laptop CAN Transceiver | USB to CAN Adapter Analyzer (CANable Open-Source / PCAN Tool) | 1 |
| | ST-Link V2 | Emulator / Programming Downloader for STM8/STM32 | 1 |

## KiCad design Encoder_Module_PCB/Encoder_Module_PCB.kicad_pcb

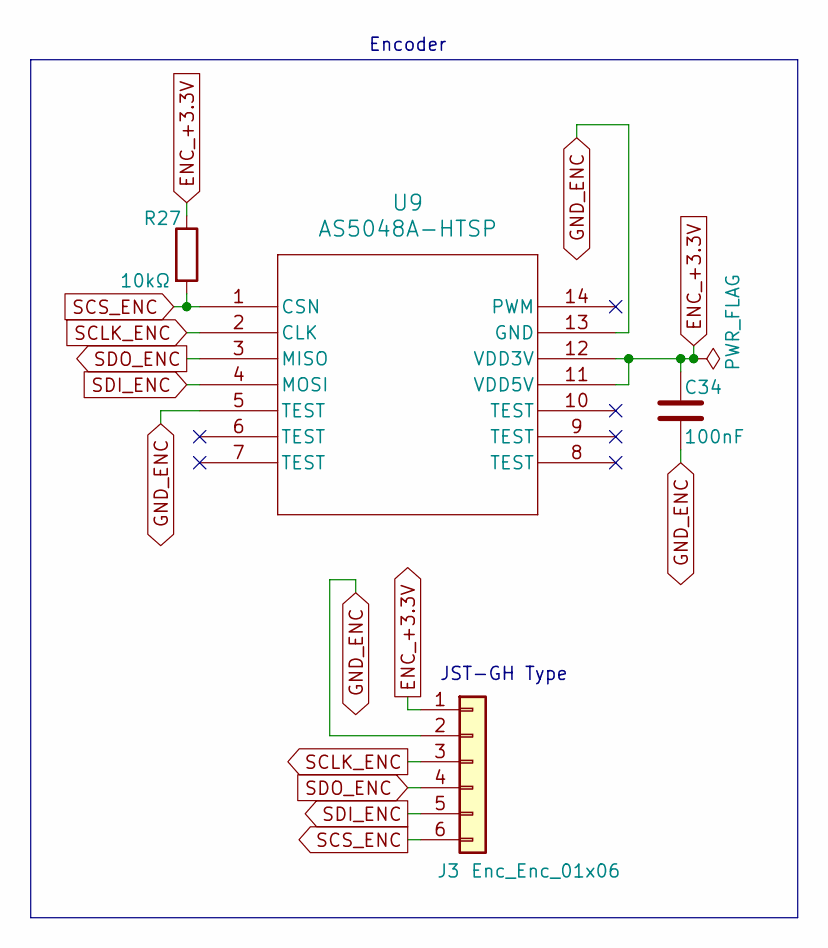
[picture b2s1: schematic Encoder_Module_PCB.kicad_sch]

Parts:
C34: 100nF; C_0603_1608Metric_Pad1.08x0.95mm_HandSolder
J3: Enc_Enc_01x06; JST-GH_CONN_SM06B-GHS-TB_JST
R27: 10kΩ; R_0603_1608Metric_Pad0.98x0.95mm_HandSolder
U9: AS5048A-HTSP; AS5048A_TSSOP14_AMS

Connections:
ENC_+3.3V: C34.1, J3.1, R27.1, U9.11 (VDD5V), U9.12 (VDD3V)
GND_ENC: C34.2, J3.2, U9.5 (TEST), U9.13 (GND)
SCLK_ENC: J3.3, U9.2 (CLK)
SCS_ENC: J3.6, R27.2, U9.1 (CSN)
SDI_ENC: J3.5, U9.4 (MOSI)
SDO_ENC: J3.4, U9.3 (MISO)

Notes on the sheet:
JST-GH Type
Encoder

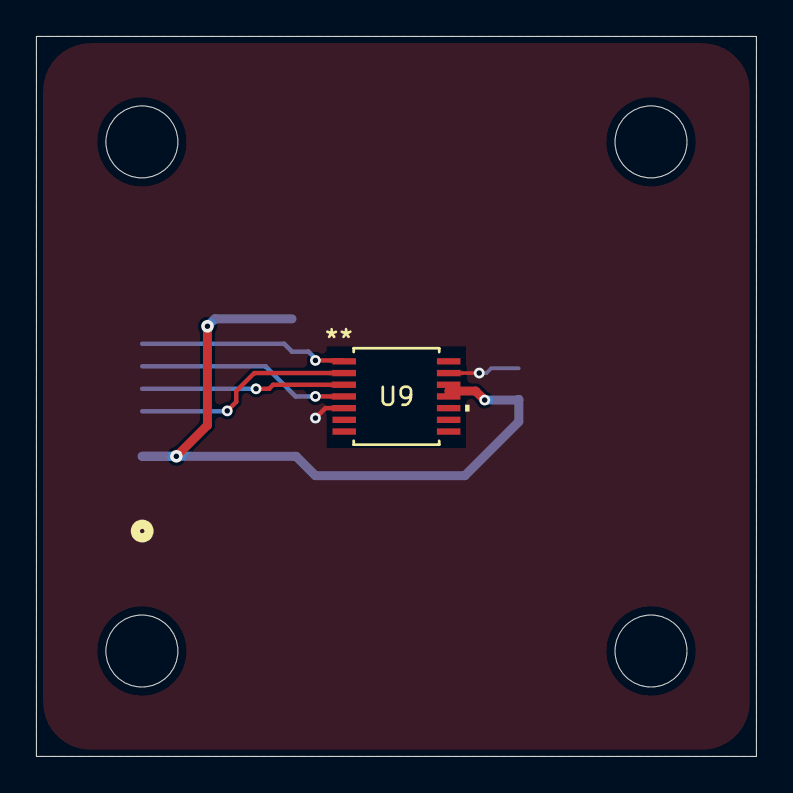
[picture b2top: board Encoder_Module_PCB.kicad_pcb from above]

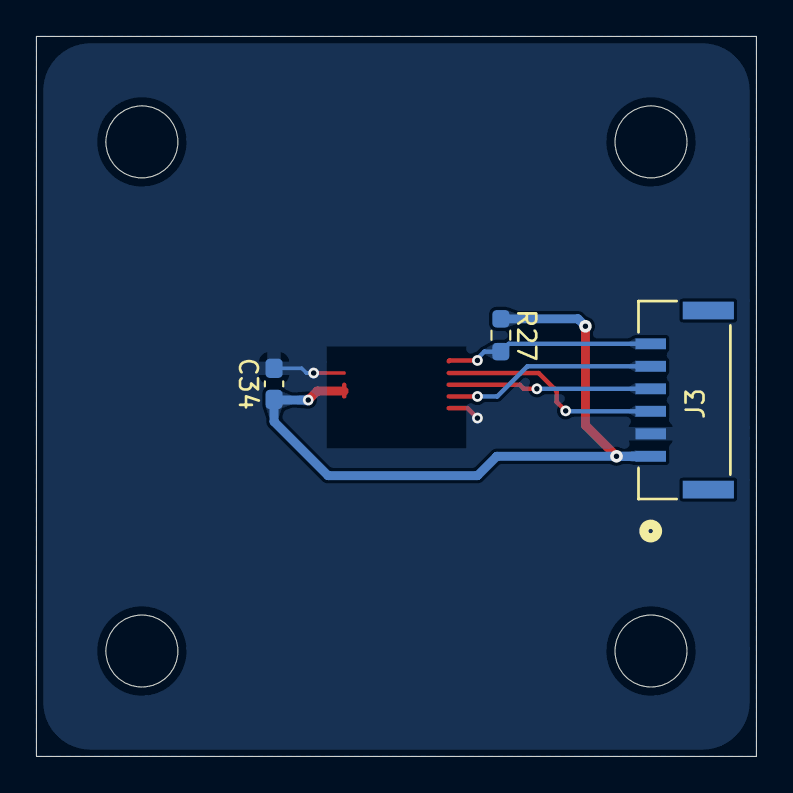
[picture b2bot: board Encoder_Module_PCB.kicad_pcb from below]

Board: 2 copper layers, 40.0 x 40.0 mm, 4 parts (3 on the bottom side), 6 nets.

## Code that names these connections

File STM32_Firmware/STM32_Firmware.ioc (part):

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Mcu.Name=STM32F405RGTx
Mcu.Package=LQFP64
Mcu.UserName=STM32F405RGTx
PA0-WKUP.Signal=ADCx_IN0
PA1.Signal=ADCx_IN1
PA10.Signal=S_TIM1_CH3
PA11.Mode=Device_Only
PA11.Signal=USB_OTG_FS_DM
PA12.Mode=Device_Only
PA12.Signal=USB_OTG_FS_DP
PA13.Mode=Serial_Wire
PA13.Signal=SYS_JTMS-SWDIO
PA14.Mode=Serial_Wire
PA14.Signal=SYS_JTCK-SWCLK
PA15.GPIOParameters=GPIO_Label
PA15.GPIO_Label=SPI3_CS_ENC
PA15.Signal=GPIO_Output
PA2.Signal=ADCx_IN2
PA3.Signal=ADCx_IN3
PA8.Signal=S_TIM1_CH1
PA9.Signal=S_TIM1_CH2
PB13.Mode=PWM Generation1 CH1 CH1N
PB13.Signal=TIM1_CH1N
PB14.Mode=Output Compare2 CH2 CH2N
PB14.Signal=TIM1_CH2N
PB15.Mode=Output Compare3 CH3 CH3N
PB15.Signal=TIM1_CH3N
PB3.Mode=Full_Duplex_Master
PB3.Signal=SPI1_SCK
PB4.Mode=Full_Duplex_Master
PB4.Signal=SPI1_MISO
PB5.Mode=Full_Duplex_Master
PB5.Signal=SPI1_MOSI
PB8.Mode=CAN_Activate
PB8.Signal=CAN1_RX
PB9.Mode=CAN_Activate
PB9.Signal=CAN1_TX
PC0.GPIOParameters=GPIO_Label
PC0.GPIO_Label=DRV_nFAULT
PC0.Signal=GPXTI0
PC1.GPIOParameters=GPIO_Label
PC1.GPIO_Label=DRV_EN_GATE
PC1.Signal=GPIO_Output
PC10.Mode=Full_Duplex_Master
PC10.Signal=SPI3_SCK
PC11.Mode=Full_Duplex_Master
PC11.Signal=SPI3_MISO
PC12.Mode=Full_Duplex_Master
PC12.Signal=SPI3_MOSI
PC2.GPIOParameters=GPIO_Label
PC2.GPIO_Label=DRV_DC_CAL
PC2.Signal=GPIO_Output
PD2.GPIOParameters=GPIO_Label
PD2.GPIO_Label=SPI1_CS_DRV
PD2.Signal=GPIO_Output
PH0-OSC_IN.Mode=HSE-External-Oscillator
PH0-OSC_IN.Signal=RCC_OSC_IN
PH1-OSC_OUT.Mode=HSE-External-Oscillator
PH1-OSC_OUT.Signal=RCC_OSC_OUT
RCC.HSE_VALUE=25000000
RCC.SYSCLKFreq_VALUE=16000000
board=custom
